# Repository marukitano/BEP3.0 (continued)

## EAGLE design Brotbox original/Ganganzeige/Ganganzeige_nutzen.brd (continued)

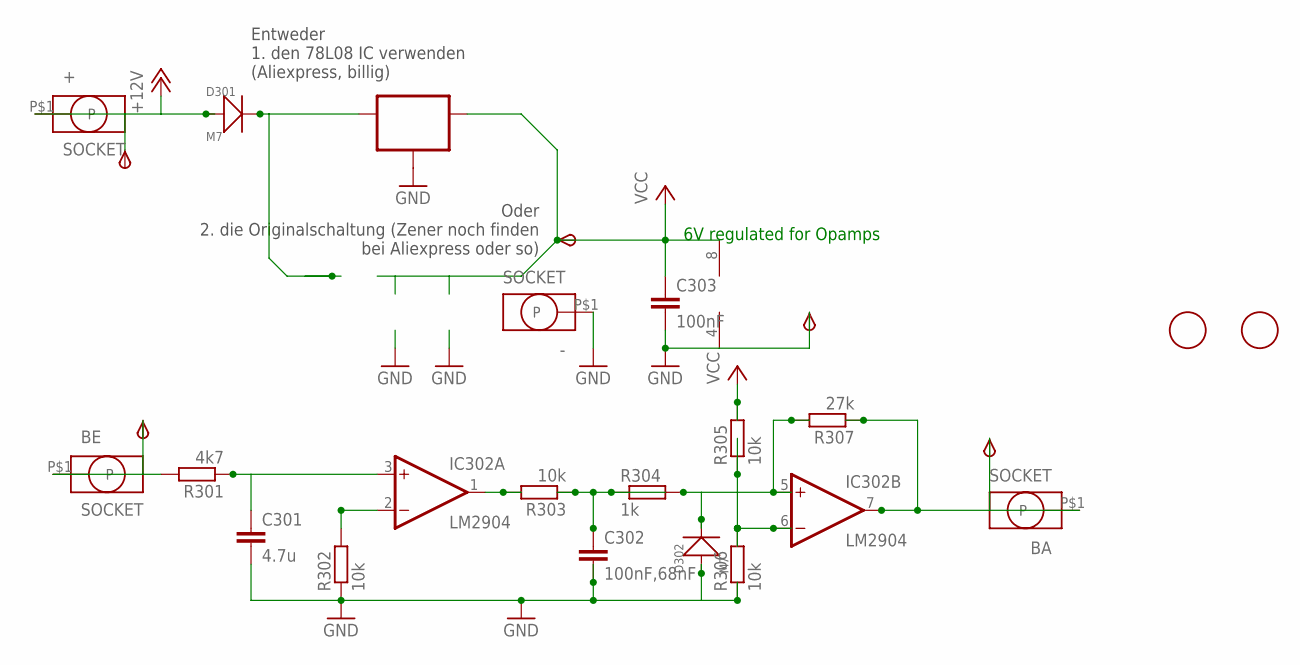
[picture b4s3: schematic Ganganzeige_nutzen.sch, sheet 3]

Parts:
6V: TPSB2.0; B2.0
+: SOCKET; ID2.5MM
+12V: TPSB2.0; B2.0
-: SOCKET; ID2.5MM
AUS: TPSB2.0; B2.0
BA: SOCKET; ID2.5MM
BE: SOCKET; ID2.5MM
C301: 4.7u; C0805K
C302: 100nF,68nF; C0805K
C303: 100nF; C0805K
D301, D302: M7; DO-214AC
EIN: TPSB2.0; B2.0
FID301, FID302: FIDUCIAL; FIDUCIAL_1MM
GND: TPSB2.0; B2.0
IC301: 5V/6V oder 8V Regler; SOT89_ROUND
IC302: LM2904; SO08
R301: 4k7; R0805
R302, R303, R305, R306: 10k; R0805
R304: 1k; R0805
R307: 27k; R0805

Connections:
+12V: +.P$1, +12V.TP, D301.1 (+); also elsewhere on the board
+12V1: AUS.TP, BA.P$1, IC302.7 (OUT), R307.1
GND: -.P$1, C301.2, C302.2, C303.2, D302.1 (+), GND.TP, IC301.2 (GND), IC301.2@1 (GND), IC302.4 (V-), R302.1, R306.1; also elsewhere on the board
unnamed: IC302.2 (-IN), R302.2
unnamed: BE.P$1, EIN.TP, R301.2
unnamed: C301.1, IC302.3 (+IN), R301.1
unnamed: D301.2 (-), IC301.3 (IN)
unnamed: IC302.1 (OUT), R303.2
unnamed: C302.1, R303.1, R304.1
unnamed: D302.2 (-), IC302.5 (+IN), R304.2, R307.2
unnamed: IC302.6 (-IN), R305.1, R306.2
VCC: 6V.TP, C303.1, IC301.1 (OUT), IC302.8 (V+), R305.2; also elsewhere on the board

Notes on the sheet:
6V regulated for Opamps
Entweder 1. den 78L08 IC verwenden (Aliexpress, billig)
Oder 2. die Originalschaltung (Zener noch finden bei Aliexpress oder so)

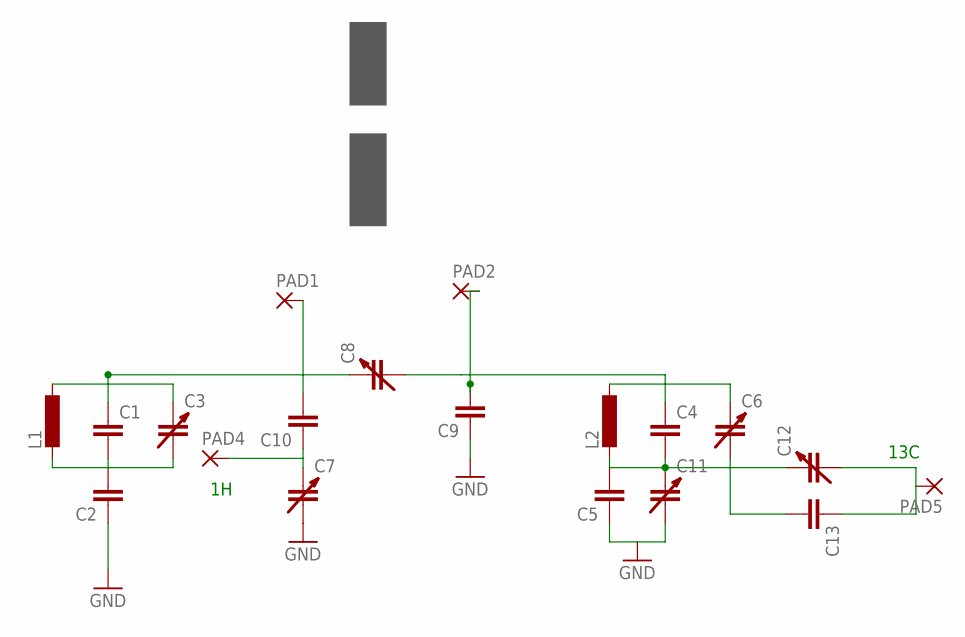
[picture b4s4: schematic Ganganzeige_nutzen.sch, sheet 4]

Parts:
C1, C2, C4, C5, C9, C10, C13: C-EUC055X055_HIGH_DENSITY; C055X055_HD
C3, C6, C7, C8, C11, C12: CTRIM-EUVOLTRONICS_JZ_SERIES; VOLTRONICS_JZ
L1, L2: L-EU6WDG_0.5MM_SELFWOUND_COIL; 6WDG_0.5MM
PAD1, PAD2: SMD2; SMD1,27-2,54
PAD4, PAD5: 1,6/0,9

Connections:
GND: C2.1, C5.1, C7.2, C9.1, C11.2; also elsewhere on the board
unnamed: C1.2, C2.2, C3.2, L1.2
unnamed: C4.2, C5.2, C6.2, C11.1, C12.1, C13.2, L2.2
unnamed: C4.1, C6.1, C8.2, C9.2, L2.1, PAD2.1
unnamed: C7.1, C10.1, PAD4.1
unnamed: C1.1, C3.1, C8.1, C10.2, L1.1, PAD1.1
unnamed: C12.2, C13.1, PAD5.1

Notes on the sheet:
13C

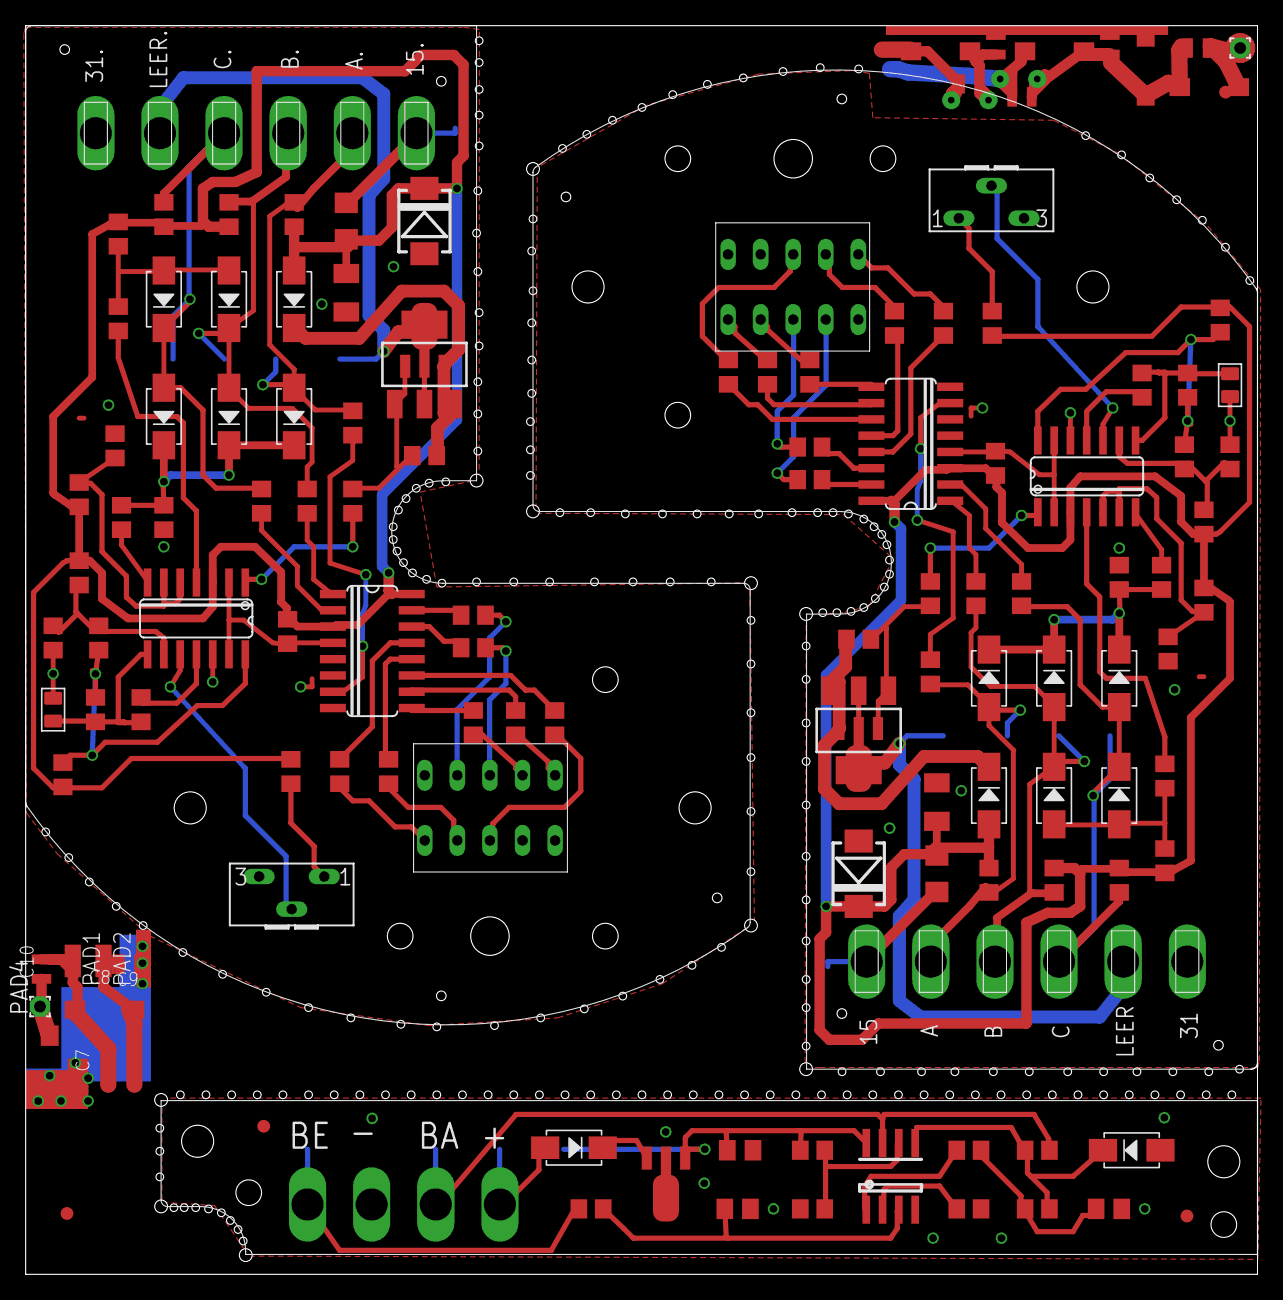
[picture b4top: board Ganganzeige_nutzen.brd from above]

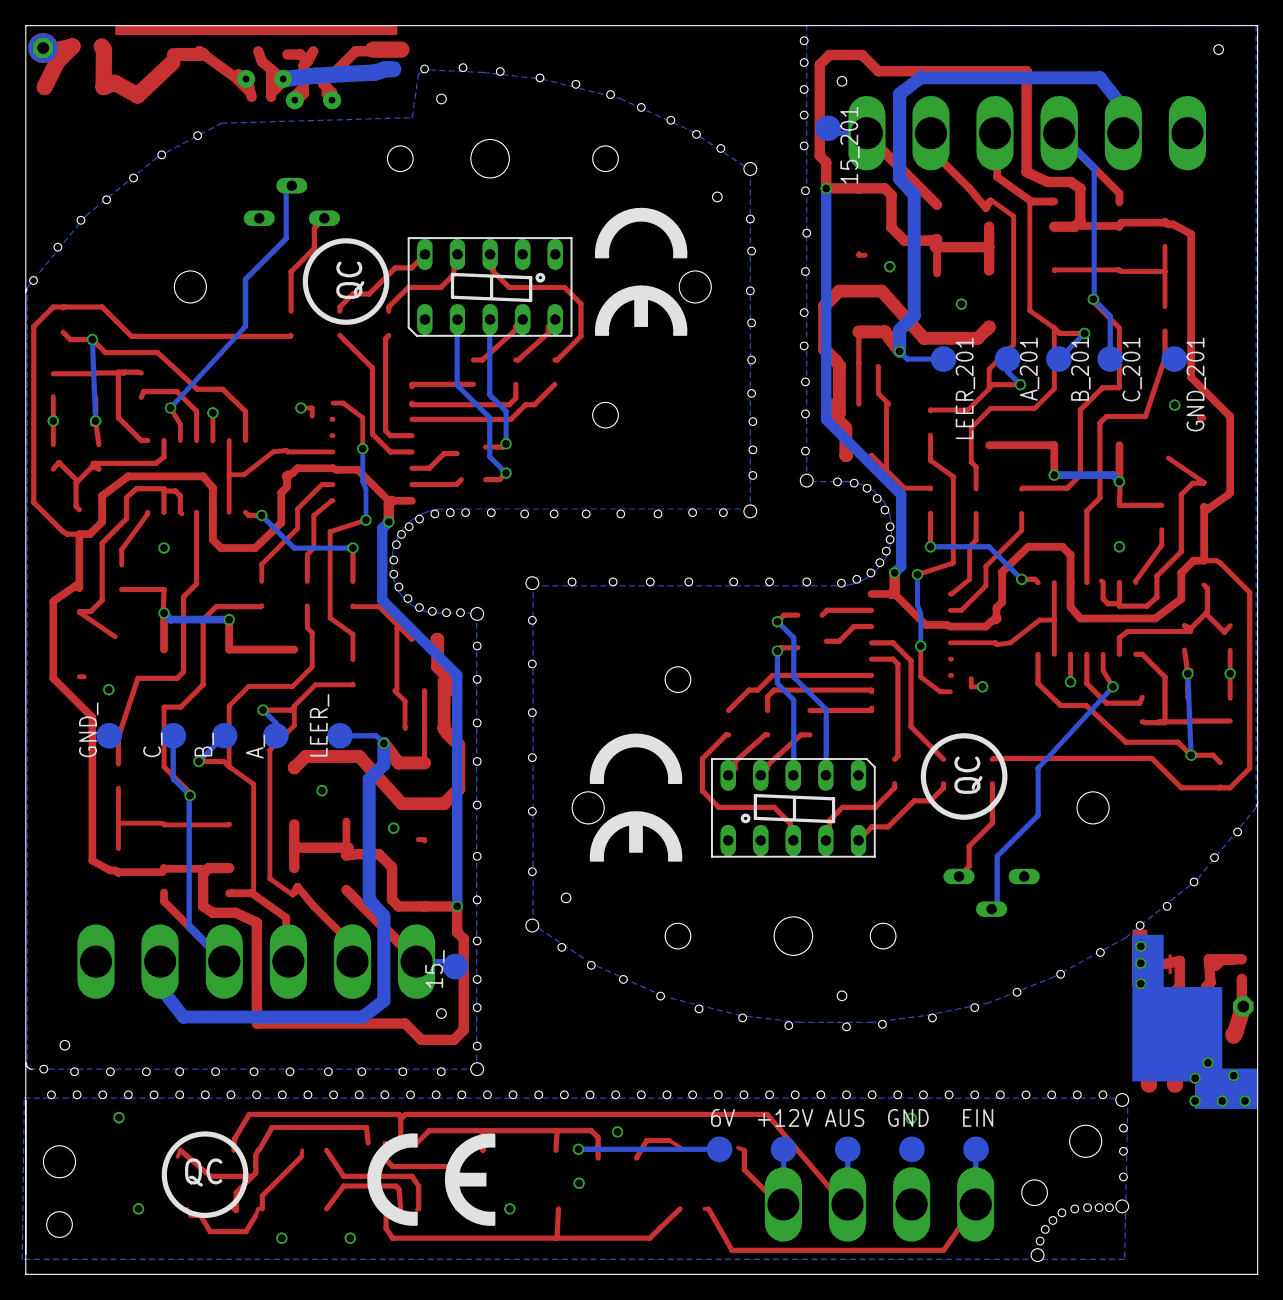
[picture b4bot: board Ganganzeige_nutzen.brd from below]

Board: 2 copper layers, 96.1 x 97.4 mm, 163 parts (22 on the bottom side), 88 nets.

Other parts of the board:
U$1, U$2, U$3: CE_10.00

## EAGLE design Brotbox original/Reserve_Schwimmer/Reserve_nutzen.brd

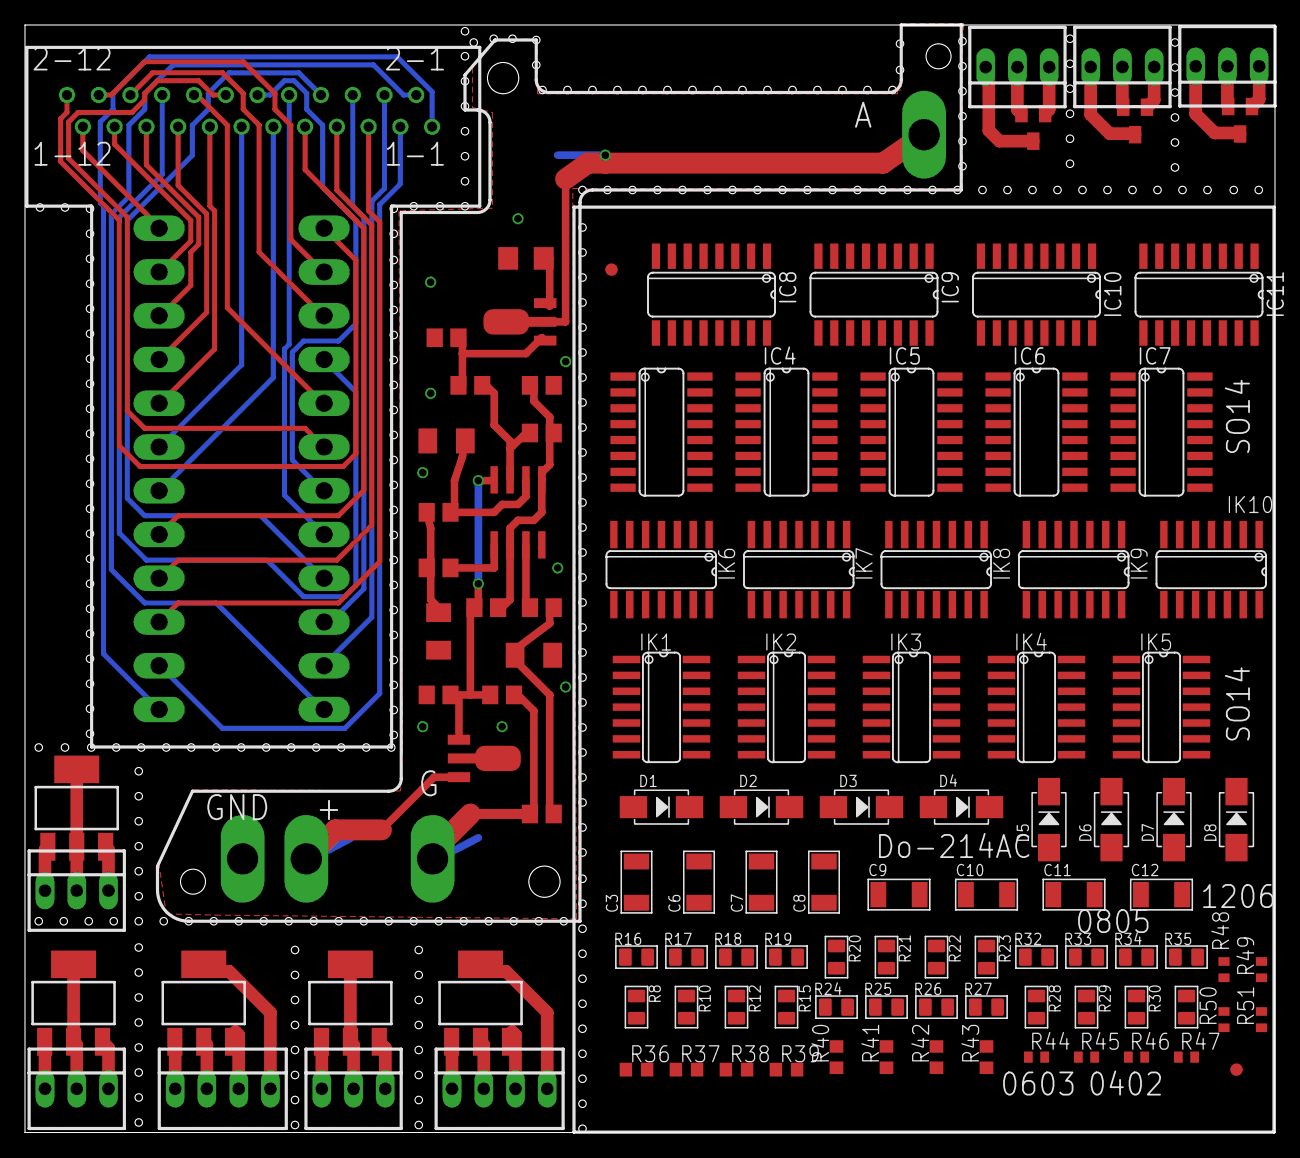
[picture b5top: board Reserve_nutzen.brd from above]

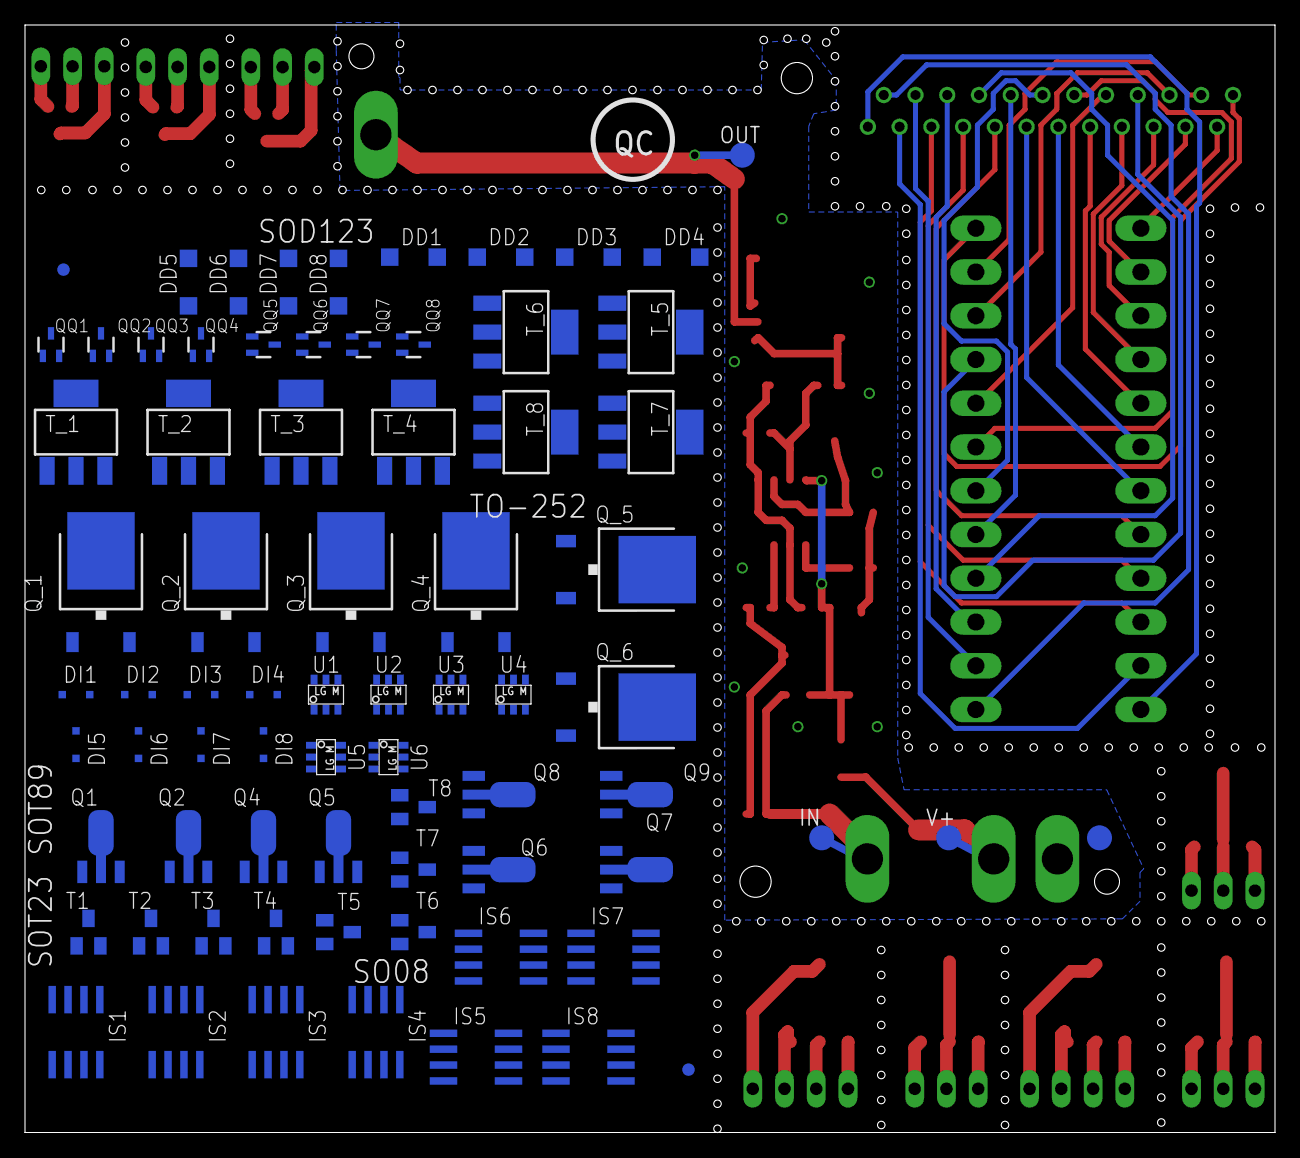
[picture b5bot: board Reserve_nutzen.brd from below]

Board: 2 copper layers, 100.0 x 88.6 mm, 191 parts (74 on the bottom side), 68 nets.

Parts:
+: SOCKET; ID2.5MM
A: SOCKET; ID2.5MM
C1: (100u); C1206K
C2, C5: 100u; C1206K
C3, C6, C7, C8, C9, C10, C11, C12: 100u; C1206
C4: 100nF; C0805
D1, D2, D3, D4, D5, D6, D7, D8: 1N4007; DO-214AC
DD1, DD2, DD3, DD4, DD5, DD6, DD7, DD8: SOD123
DI1, DI2, DI3, DI4, DI5, DI6, DI7, DI8: SOD323-R
FID1_: FID2; FIDUCIAL_1MM
FID2: FID1; FIDUCIAL_1MM
FID3_, FID4: FIDUCIAL; FIDUCIAL_1MM
G: SOCKET; ID2.5MM
GND: SOCKET; ID2.5MM
GND_: TPSB2.0; B2.0
IC1: LM2904; SO08
IC2: 70L06; SOT89_ROUND
IC3, IC4, IC5, IC6, IC7, IC8, IC9, IC10, IC11: 4028; SO16
IK1, IK2, IK3, IK4, IK5, IK6, IK7, IK8, IK9, IK10: LM339; SO14
IN: TPSB2.0; B2.0
IS1, IS2, IS3, IS4, IS5, IS6, IS7, IS8: 555; SO08
OUT: TPSB2.0; B2.0
Q1, Q2, Q3, Q4, Q5, Q6, Q7, Q8, Q9: MY; SOT89
Q49, Q52, Q55: BCP53T1; SOT223
Q50, Q56: BSP452T1; SOT223
Q51, Q54, Q57: BC818-16SMD; SOT23-BEC
QQ1, QQ2, QQ3, QQ4, QQ5, QQ6, QQ7, QQ8: SOT323
Q_1, Q_2, Q_3, Q_4, Q_5, Q_6: SPD30P06PTO252; TO252
R1, R6, R11, R13: 10k; R0805
R2: 4k7; R0805
R3: 13; R1206
R4, R5, R9: 100k; R0805
R7: 2k2; R0805
R8, R10, R12, R15, R16, R17, R18, R19, R20, R21, R22, R23, R24, R25, R26, R27, R28, R29, R30, R31, R32, R33, R34, R35: 4701; R0805
R14: 2.2k; R0805
R36, R37, R38, R39, R40, R41, R42, R43: R0603
R44, R45, R46, R47, R48, R49, R50, R51: R0402
T1, T2, T3, T4, T5, T6, T7, T8: J1; SOT23-BEC
T_1, T_2, T_3, T_4, T_5, T_6, T_7, T_8: SOT223
U1, U2, U3, U4, U5, U6: NUP4304SOT457_R; SOT457R_PHILIPS
U$1: TESTADAPTER-24P; 24-PIN-TESTADAPTER
U$3: TESTADAPTER-24P24-PIN-ANSCHLUSS; 24-PIN-ANSCHLUSS
V+: TPSB2.0; B2.0
X68, X70, X75, X77, X78, X80: 22-23-2031
X69, X79: 22-23-2041

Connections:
+12V: +.P$1, IC2.3, V+.TP
GND: C1.2, C2.2, C4.2, C5.2, GND.P$1, GND_.TP, IC1.4, IC2.2, IC2.2@1, R3.2, R7.2, R13.1
GND1: IK1.12, IK2.12, IK3.12, IK4.12, IK5.12, IK6.12, IK7.12, IK8.12, IK9.12, IK10.12, IS1.1, IS2.1, IS3.1, IS4.1, IS5.1, IS6.1, IS7.1, IS8.1
unnamed: C2.1, R5.1, R6.2
unnamed: Q3.1, R2.1, R7.1
unnamed: C1.1, R4.1, R9.2
unnamed: C5.1, IC1.6, R9.1
unnamed: IC1.2, IC1.5, R11.1, R13.2, R14.2
unnamed: G.P$1, IN.TP, R1.2, R5.2
unnamed: Q3.3, R3.1
unnamed: IC1.3, R6.1
unnamed: IC1.7, R2.2, R14.1
unnamed: A.P$1, OUT.TP, Q3.2
unnamed: U$1.P$2-1, U$3.P$2-1
unnamed: U$1.P$2-2, U$3.P$2-2
unnamed: U$1.P$2-3, U$3.P$2-3
unnamed: U$1.P$2-4, U$3.P$2-4
unnamed: U$1.P$2-5, U$3.P$2-5
unnamed: U$1.P$2-6, U$3.P$2-6
unnamed: U$1.P$2-7, U$3.P$2-7
unnamed: U$1.P$2-8, U$3.P$2-8
unnamed: U$1.P$2-9, U$3.P$2-9
unnamed: U$1.P$2-10, U$3.P$2-10
unnamed: U$1.P$2-11, U$3.P$2-11
unnamed: U$1.P$2-12, U$3.P$2-12
unnamed: U$1.P$1-2, U$3.P$1-2
unnamed: U$1.P$1-3, U$3.P$1-3
unnamed: U$1.P$1-4, U$3.P$1-4
unnamed: U$1.P$1-6, U$3.P$1-6
unnamed: U$1.P$1-7, U$3.P$1-7
unnamed: U$1.P$1-8, U$3.P$1-8
unnamed: U$1.P$1-9, U$3.P$1-9
unnamed: U$1.P$1-10, U$3.P$1-10
unnamed: U$1.P$1-11, U$3.P$1-11
unnamed: U$1.P$1-12, U$3.P$1-12
unnamed: U$1.P$1-5, U$3.P$1-5
unnamed: U$1.P$1-1, U$3.P$1-1
unnamed: Q49.1, X68.1
unnamed: Q49.2, X68.2
unnamed: Q49.3, X68.3
unnamed: Q50.1, X69.1
unnamed: Q50.2, X69.2
unnamed: Q50.3, X69.3
unnamed: Q50.4, X69.4
unnamed: Q51.B, X70.1
unnamed: Q51.E, X70.2
unnamed: Q51.C, X70.3
unnamed: Q52.1, X75.1
unnamed: Q52.2, X75.2
unnamed: Q52.3, X75.3
unnamed: Q54.B, X77.1
unnamed: Q54.E, X77.2
unnamed: Q54.C, X77.3
unnamed: Q55.1, X78.1
unnamed: Q55.2, X78.2
unnamed: Q55.3, X78.3
unnamed: Q56.1, X79.1
unnamed: Q56.2, X79.2
unnamed: Q56.3, X79.3
unnamed: Q56.4, X79.4
unnamed: Q57.B, X80.1
unnamed: Q57.E, X80.2
unnamed: Q57.C, X80.3
unnamed: IC1.1, R4.2
V+: IK1.3, IK2.3, IK3.3, IK4.3, IK5.3, IK6.3, IK7.3, IK8.3, IK9.3, IK10.3, IS1.8, IS2.8, IS3.8, IS4.8, IS5.8, IS6.8, IS7.8, IS8.8
VCC: C4.1, IC1.8, IC2.1, R1.1, R11.2
VDD: IC3.16, IC4.16, IC5.16, IC6.16, IC7.16, IC8.16, IC9.16, IC10.16, IC11.16
VSS: IC3.8, IC4.8, IC5.8, IC6.8, IC7.8, IC8.8, IC9.8, IC10.8, IC11.8

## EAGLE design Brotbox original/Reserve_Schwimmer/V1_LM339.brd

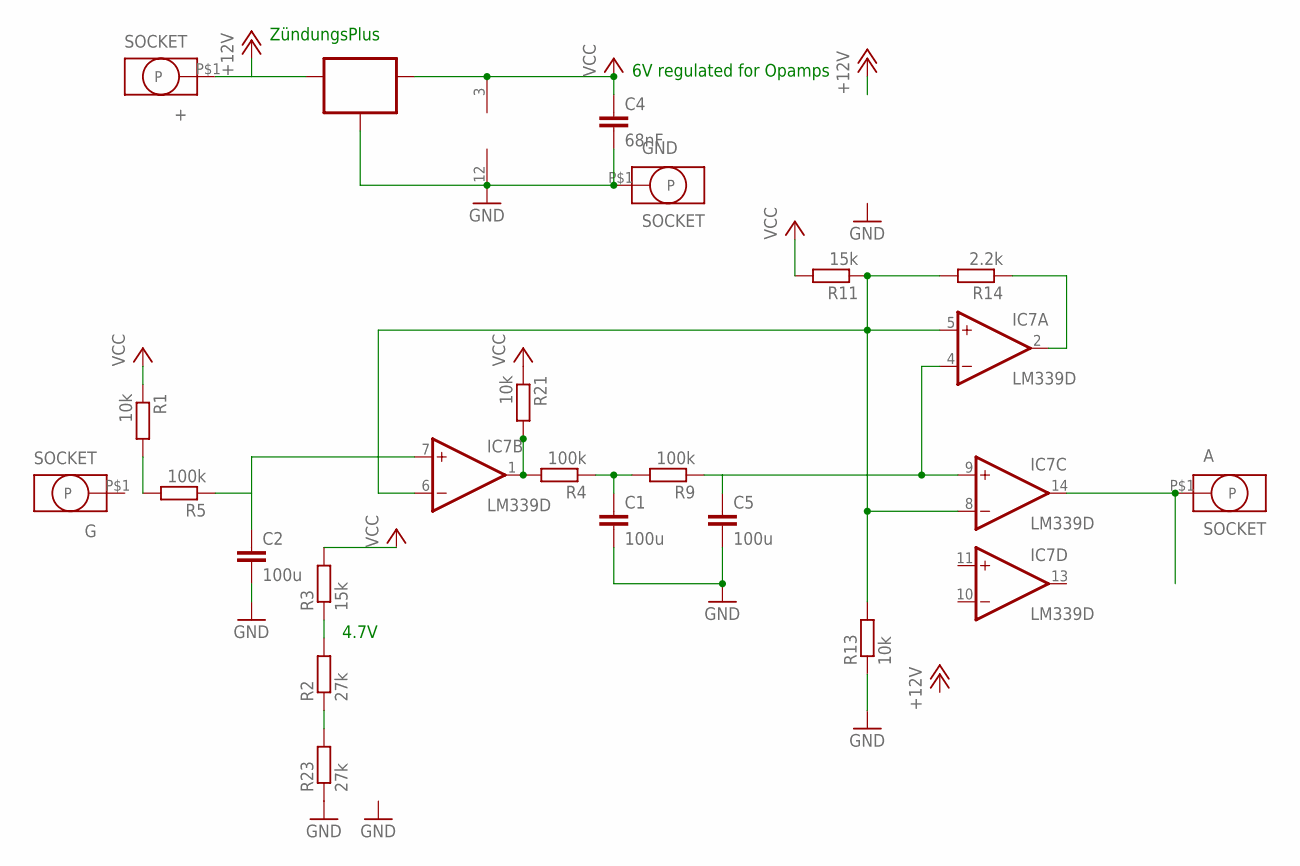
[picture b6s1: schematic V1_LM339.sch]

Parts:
+: SOCKET; ID2.5MM
A: SOCKET; ID2.5MM
C1, C2, C5: 100u; C1206K
C4: 68nF; C1206K
G: SOCKET; ID2.5MM
GND: SOCKET; ID2.5MM
IC2: 78LXXSOT89_ROUND; SOT89_ROUND
IC7: LM339D; SO14
R1, R13, R21: 10k; R0805
R2, R23: 27k; R0805
R3, R11: 15k; R0805
R4, R5, R9: 100k; R0805
R14: 2.2k; R0805

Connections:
+12V: +.P$1, IC2.3 (IN)
GND: C1.2, C2.2, C4.2, C5.2, GND.P$1, IC2.2 (GND), IC2.2@1 (GND), IC7.12 (GND), R13.1, R23.1
unnamed: C2.1, IC7.7 (+IN), R5.1
unnamed: R2.2, R3.1
unnamed: C1.1, R4.1, R9.2
unnamed: C5.1, IC7.4 (-IN), IC7.9 (+IN), R9.1
unnamed: IC7.5 (+IN), IC7.6 (-IN), IC7.8 (-IN), R11.1, R13.2, R14.2
unnamed: R1.2, R5.2
unnamed: R2.1, R23.2
unnamed: A.P$1, IC7.14 (OUT)
unnamed: IC7.2 (OUT), R14.1
unnamed: IC7.1 (OUT), R4.2, R21.2
VCC: C4.1, IC2.1 (OUT), IC7.3 (V+), R1.1, R3.2, R11.2, R21.1

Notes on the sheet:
6V regulated for Opamps
ZündungsPlus
4.7V

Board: 2 copper layers, 21 parts (0 on the bottom side), 13 nets, no tracks yet.
